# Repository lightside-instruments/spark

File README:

Spark is a modular open-source hardware platform
base board and enclosure for use as development kit for programmable
network elements.

The project includes KiCAD project with schematics
and PCB layout sources, BOM, and technical documentation for
production of board with 6x SFP+ interfaces and a 96board
extension interface for the connection of a control board
(FPGA or ASIC)  e.g. Ultra96 from Avnet
and up to 3 optional extension boards:
* glue logic for low speed signals from the optical modules
* GNSS controlled oscillators
* other interface boards, sensor boards, etc.

The project includes also technical documentation for production of
mechanical enclosure - 19 inch 1U rack mountable ESD Acrylic box compatibe
with the base board.

The project is published by Lightside Instruments AS
under TAPR Open Hardware License. Read the LICENSE file
for details.

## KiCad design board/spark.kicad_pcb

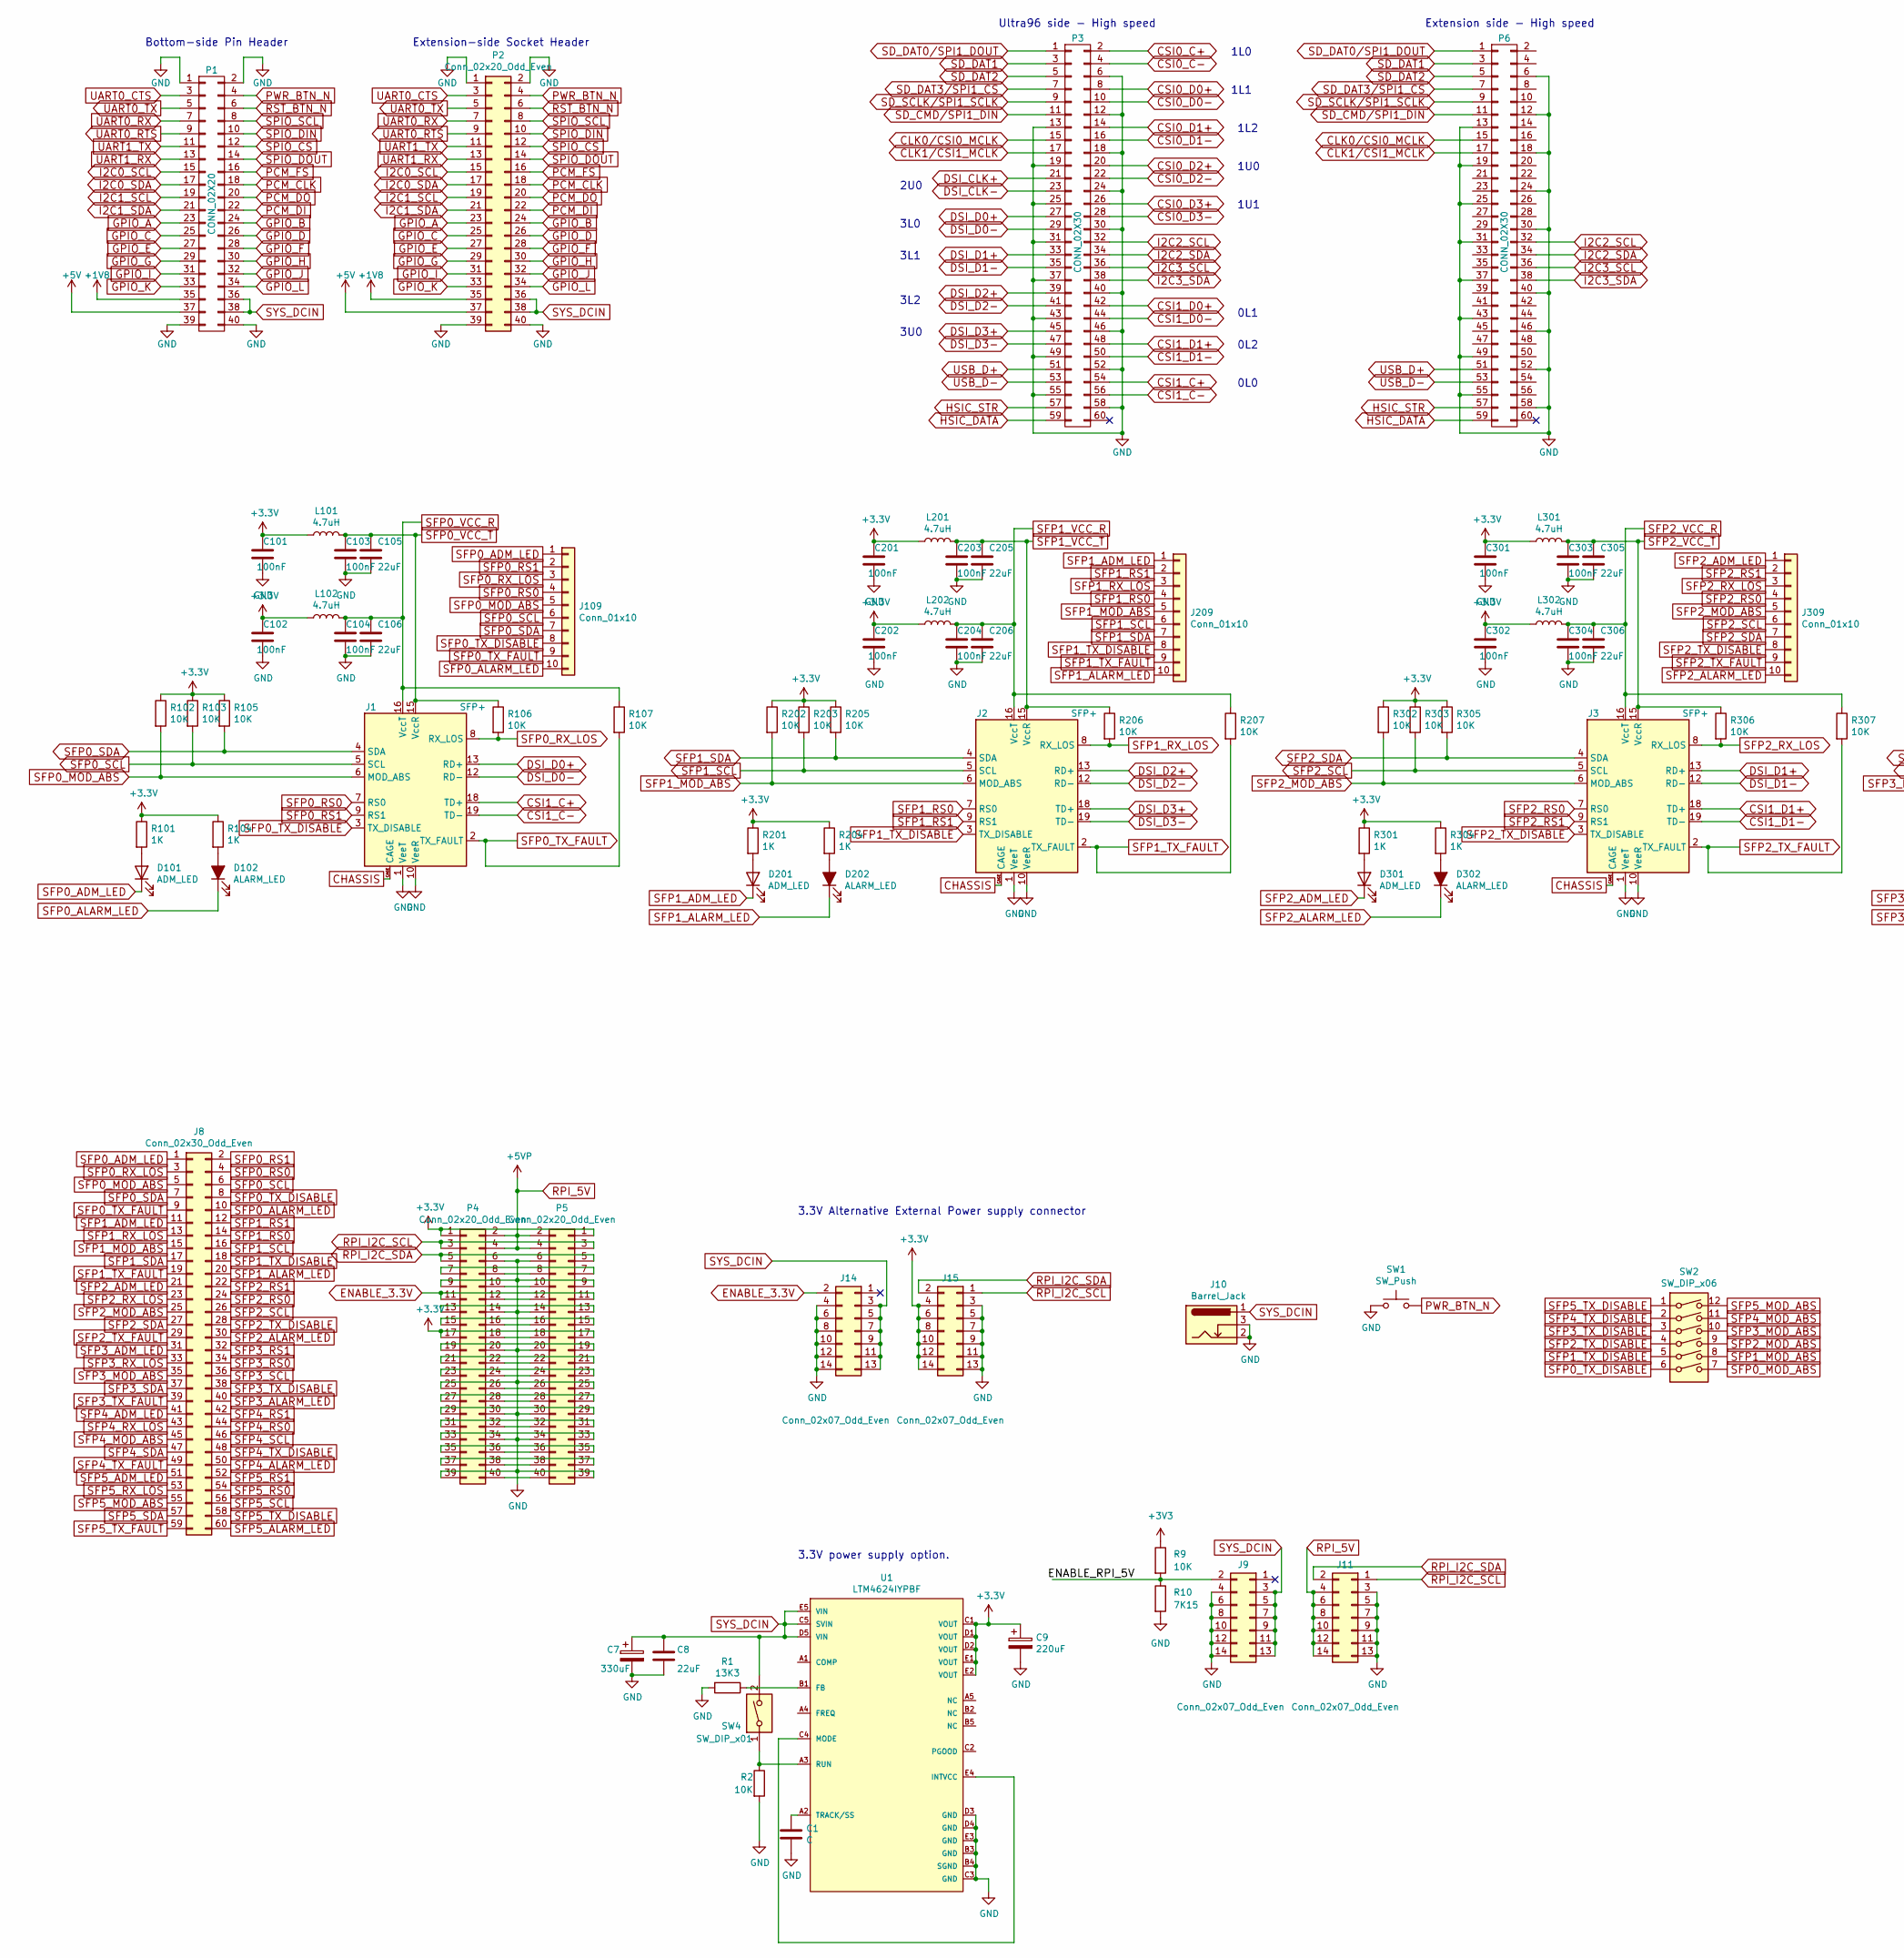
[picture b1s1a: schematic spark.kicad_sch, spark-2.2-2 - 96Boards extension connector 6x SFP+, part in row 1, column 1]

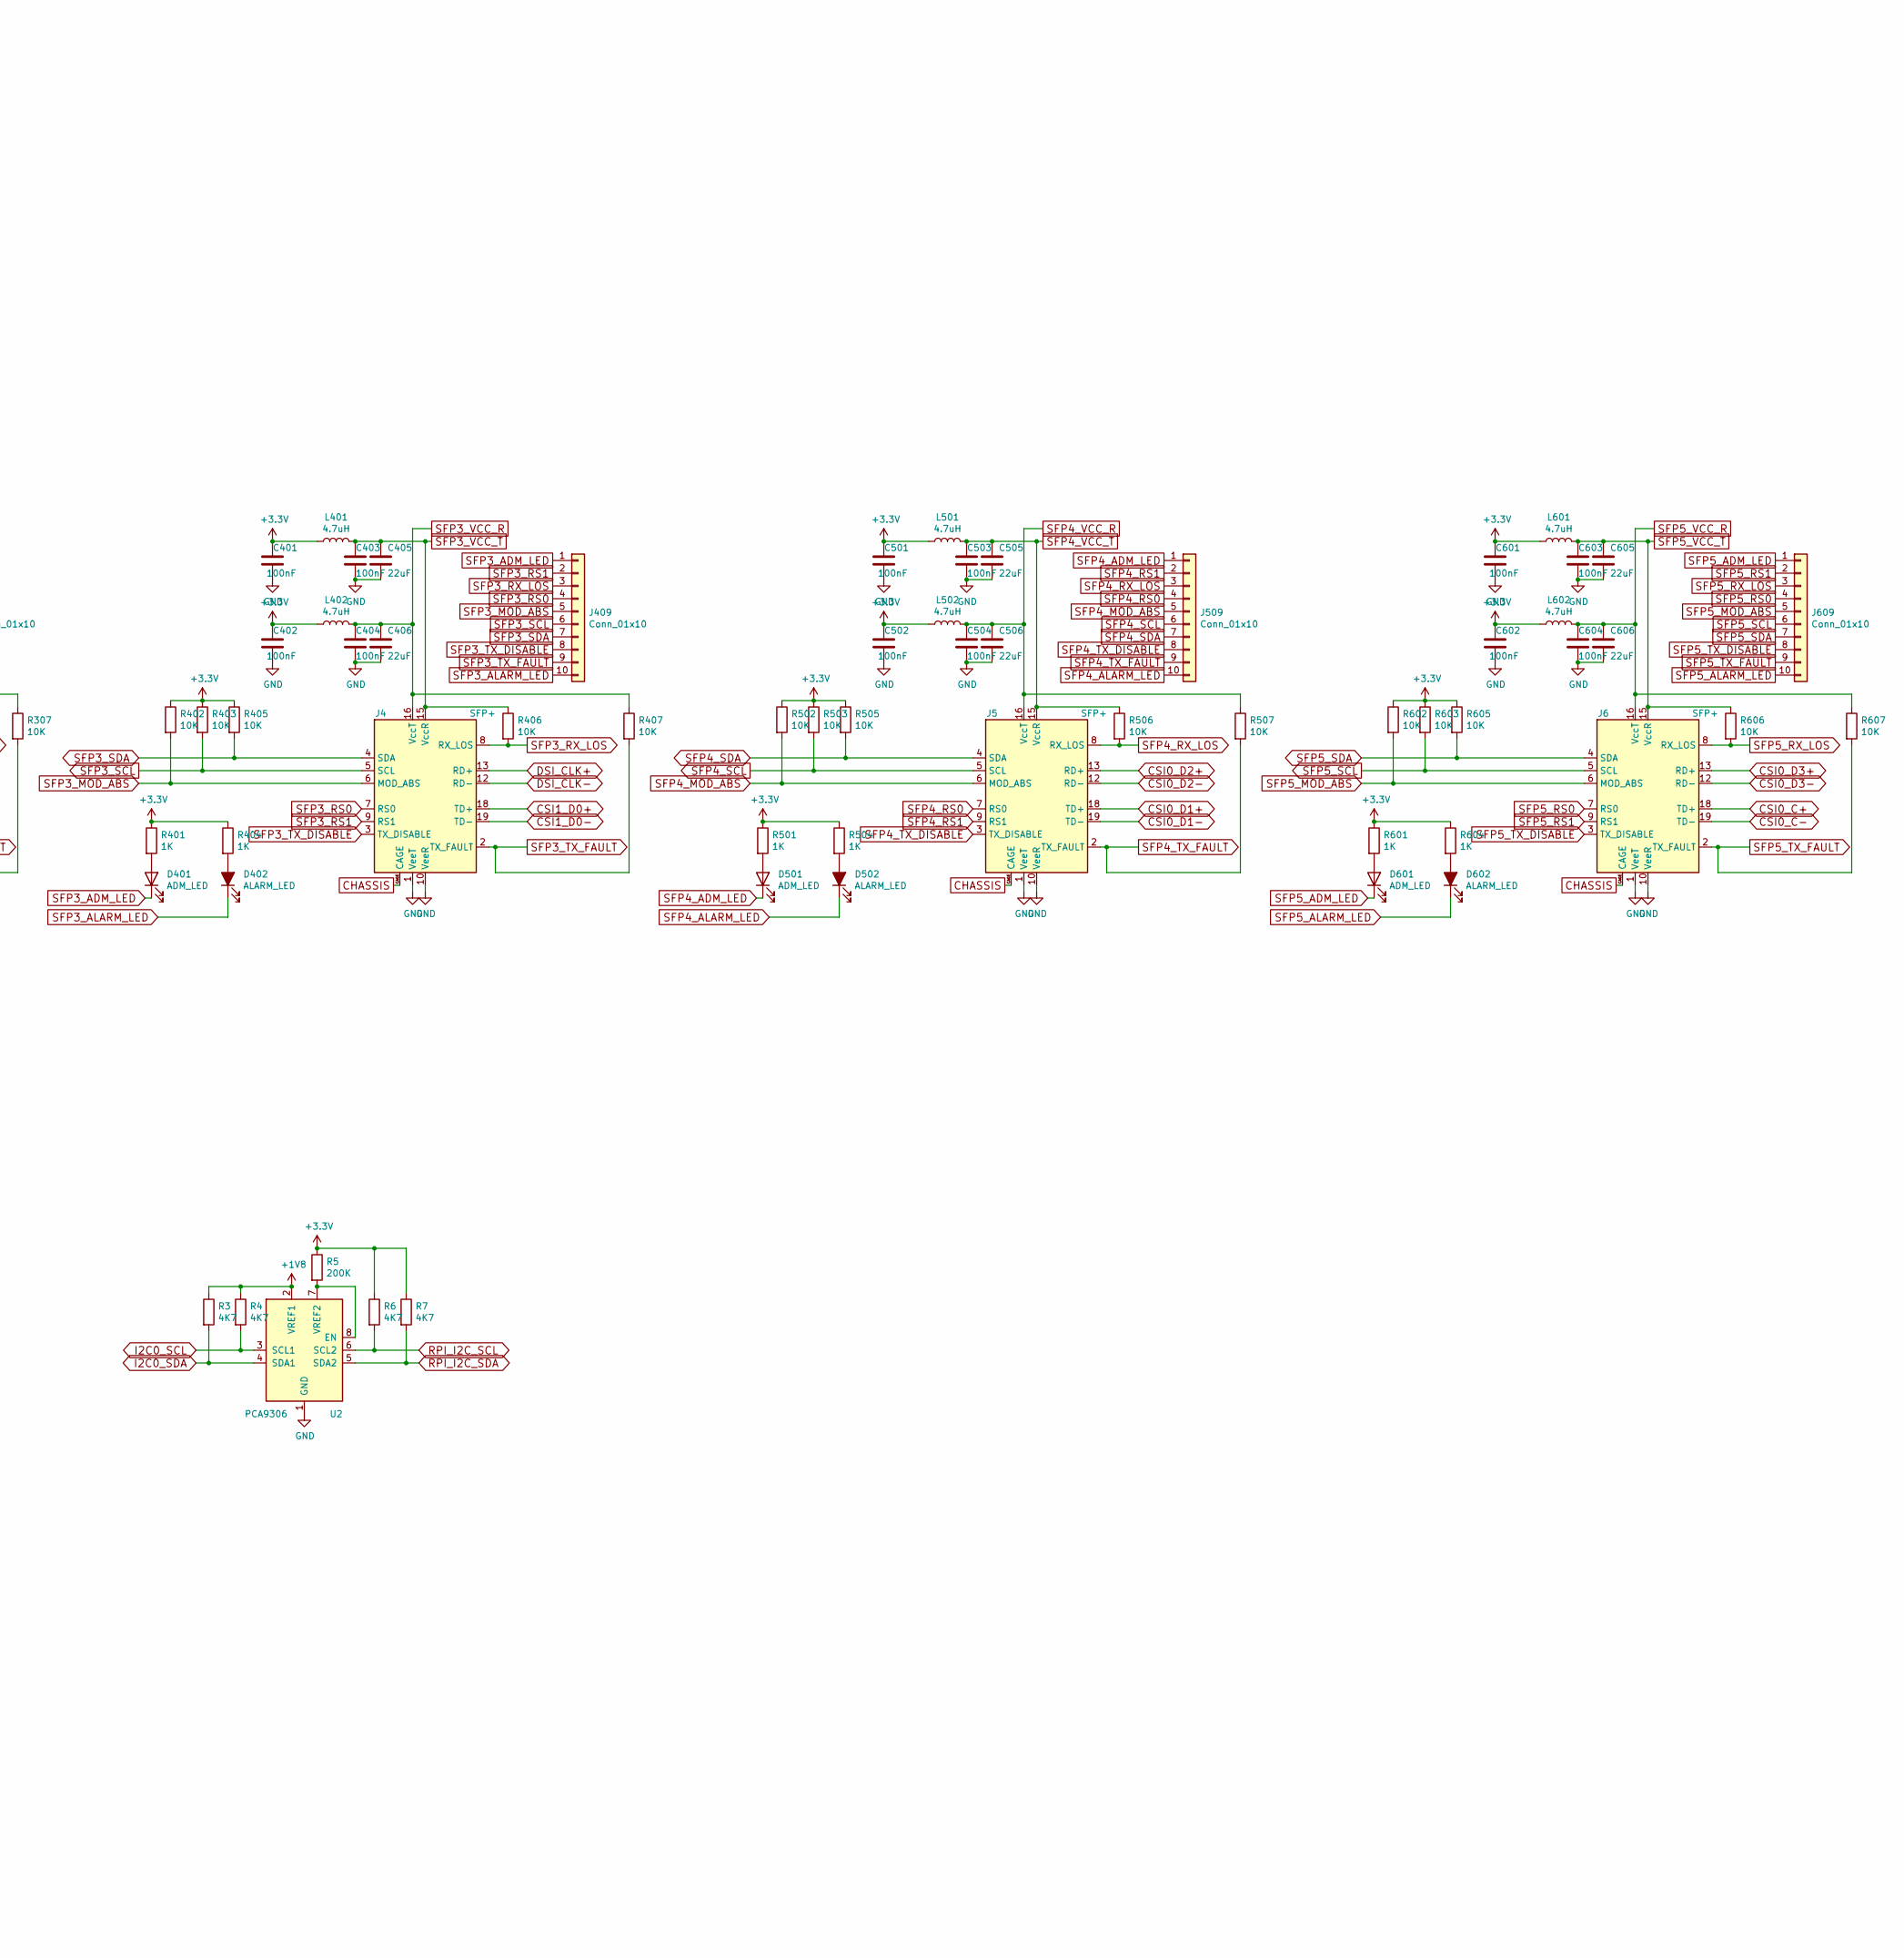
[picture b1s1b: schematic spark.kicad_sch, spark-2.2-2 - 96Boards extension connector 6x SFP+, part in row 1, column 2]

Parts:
C1: C; C_0402_1005Metric
C7: 330uF; CP_EIA-7343-31_Kemet-D
C8, C105, C106, C205, C206, C305, C306, C405, C406, C505, C506, C605, C606: 22uF; CP_EIA-3528-21_Kemet-B; Mfr Part # TAJB226K016TNJ
C9: 220uF; CP_EIA-7343-31_Kemet-D
C101, C102, C103, C104, C201, C202, C203, C204, C301, C302, C303, C304, C401, C402, C403, C404, C501, C502, C503, C504, C601, C602, C603, C604: 100nF; C_0402_1005Metric
D101, D201, D301, D401, D501, D601: ADM_LED; LED_0402_1005Metric
D102, D202, D302, D402, D502, D602: ALARM_LED; LED_0402_1005Metric
J1, J2, J3, J4, J5, J6: SFP+; molex-sfp-plus-747540-101
J8: Conn_02x30_Odd_Even; PinHeader_2x30_P2.00mm_Vertical_SMD
J9, J11, J14, J15: Conn_02x07_Odd_Even; PinSocket_2x07_P2.00mm_Vertical_SMD
J10: Barrel_Jack; PJ1-021-SMT-TR
J109, J209, J309, J409, J509, J609: Conn_01x10; sfp_header
L101, L102, L201, L202, L301, L302, L401, L402, L501, L502, L601, L602: 4.7uH; L_1210_3225Metric
P1: CONN_02X20; Pin_Header_SMD_2x20_Pitch2mm; Mfr Part # 87759-4051
P2: Conn_02x20_Odd_Even; Socket_Strip_SMD_2x20_Pitch2mm_Alignment_Pin
P3: CONN_02X30; 61083-063400LF; Mfr Part # 61083-064400LF
P4, P5: Conn_02x20_Odd_Even; PinSocket_2x20_P2.54mm_Vertical_Inverted_SMD_Alignment_Pin
P6: CONN_02X30; 5177983-2; Mfr Part # 5177983-2
R1: 13K3; R_0402_1005Metric
R2, R9, R102, R103, R105, R106, R107, R202, R203, R205, R206, R207, R302, R303, R305, R306, R307, R402, R403, R405, R406, R407, R502, R503, R505, R506, R507, R602, R603, R605, R606, R607: 10K; R_0402_1005Metric
R3, R4, R6, R7: 4K7; R_0402_1005Metric
R5: 200K; R_0402_1005Metric
R10: 7K15; R_0402_1005Metric
R101, R104, R201, R204, R301, R304, R401, R404, R501, R504, R601, R604: 1K; R_0402_1005Metric
SW1: SW_Push; SW_Tactile_SPST_Angled_PTS645Vx83-2LFS; Mfr Part # PTS645VK582LFS
SW2: SW_DIP_x06; SW_DIP_SPSTx06_Slide_Omron_A6H-6101_W6.15mm_P1.27mm; Mfr Part # A6H-6101
SW4: SW_DIP_x01; PinHeader_1x02_P2.54mm_Vertical
U1: LTM4624IYPBF; Analog_Devices_Inc-BGA-0-05-08-1905_Rev_C-0; output voltage 0.6-5.5V; mouser part number 584-LTM4624IY#PBF; digikey description DC DC CONVERTER 0.6-5.5V 4A
U2: PCA9306; SO-8_3.9x4.9mm_P1.27mm

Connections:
+1V8: P1.35, P2.35, R3.1, R4.1, U2.2 (VREF1)
+5V: P1.37, P2.37
/ENABLE_RPI_5V: J9.2, R9.2, R10.1
CHASSIS: J1.CAGE, J2.CAGE, J3.CAGE, J4.CAGE, J5.CAGE, J6.CAGE
CLK0/CSI0_MCLK: P3.15, P6.15
CLK1/CSI1_MCLK: P3.17, P6.17
CSI0_C+: J6.18 (TD+), P3.2
CSI0_C-: J6.19 (TD-), P3.4
CSI0_D0+: P3.8
CSI0_D0-: P3.10
CSI0_D1+: J5.18 (TD+), P3.14
CSI0_D1-: J5.19 (TD-), P3.16
CSI0_D2+: J5.13 (RD+), P3.20
CSI0_D2-: J5.12 (RD-), P3.22
CSI0_D3+: J6.13 (RD+), P3.26
CSI0_D3-: J6.12 (RD-), P3.28
CSI1_C+: J1.18 (TD+), P3.54
CSI1_C-: J1.19 (TD-), P3.56
CSI1_D0+: J4.18 (TD+), P3.42
CSI1_D0-: J4.19 (TD-), P3.44
CSI1_D1+: J3.18 (TD+), P3.48
CSI1_D1-: J3.19 (TD-), P3.50
DSI_CLK+: J4.13 (RD+), P3.21
DSI_CLK-: J4.12 (RD-), P3.23
DSI_D0+: J1.13 (RD+), P3.27
DSI_D0-: J1.12 (RD-), P3.29
DSI_D1+: J3.13 (RD+), P3.33
DSI_D1-: J3.12 (RD-), P3.35
DSI_D2+: J2.13 (RD+), P3.39
DSI_D2-: J2.12 (RD-), P3.41
DSI_D3+: J2.18 (TD+), P3.45
DSI_D3-: J2.19 (TD-), P3.47
ENABLE_3.3V: J14.2, P4.11, P5.11
GND: C1.2, C7.2, C8.2, C9.2, C101.2, C102.2, C103.2, C104.2, C105.2, C106.2, C201.2, C202.2, C203.2, C204.2, C205.2, C206.2, C301.2, C302.2, C303.2, C304.2, C305.2, C306.2, C401.2, C402.2, C403.2, C404.2, C405.2, C406.2, C501.2, C502.2, C503.2, C504.2, C505.2, C506.2, C601.2, C602.2, C603.2, C604.2, C605.2, C606.2, J1.1 (VeeT), J1.10 (VeeR), J1.11 (VeeR), J1.14 (VeeR), J1.17 (VeeT), J1.20 (VeeT), J2.1 (VeeT), J2.10 (VeeR), J2.11 (VeeR), J2.14 (VeeR), J2.17 (VeeT), J2.20 (VeeT), J3.1 (VeeT), J3.10 (VeeR), J3.11 (VeeR), J3.14 (VeeR), J3.17 (VeeT), J3.20 (VeeT), J4.1 (VeeT), J4.10 (VeeR), J4.11 (VeeR), J4.14 (VeeR), J4.17 (VeeT), J4.20 (VeeT), J5.1 (VeeT), J5.10 (VeeR), J5.11 (VeeR), J5.14 (VeeR), J5.17 (VeeT), J5.20 (VeeT), J6.1 (VeeT), J6.10 (VeeR), J6.11 (VeeR), J6.14 (VeeR), J6.17 (VeeT), J6.20 (VeeT), J9.4, J9.6, J9.8, J9.10, J9.12, J9.14, J10.2, J10.3, J11.3, J11.5, J11.7, J11.9, J11.11, J11.13, J14.4, J14.6, J14.8, J14.10, J14.12, J14.14, J15.3, J15.5, J15.7, J15.9, J15.11, J15.13, P1.1, P1.2, P1.39, P1.40, P2.1, P2.2, P2.39, P2.40, P3.6, P3.12, P3.13, P3.18, P3.19, P3.24, P3.25, P3.30, P3.31, P3.37, P3.40, P3.43, P3.46, P3.49, P3.52, P3.55, P3.58, P4.6, P4.9, P4.14, P4.20, P4.25, P4.30, P4.34, P4.39, P5.6, P5.9, P5.14, P5.20, P5.25, P5.30, P5.34, P5.39, P6.6, P6.12, P6.13, P6.18, P6.19, P6.24, P6.25, P6.30, P6.31, P6.37, P6.40, P6.43, P6.46, P6.49, P6.52, P6.55, P6.58, R1.2, R2.2, R10.2, SW1.1, U1.B3 (GND), U1.B4 (SGND), U1.C3 (GND), U1.D3 (GND), U1.D4 (GND), U1.E3 (GND), U2.1 (GND)
GPIO_A: P1.23, P2.23
GPIO_B: P1.24, P2.24
GPIO_C: P1.25, P2.25
GPIO_D: P1.26, P2.26
GPIO_E: P1.27, P2.27
GPIO_F: P1.28, P2.28
GPIO_G: P1.29, P2.29
GPIO_H: P1.30, P2.30
GPIO_I: P1.31, P2.31
GPIO_J: P1.32, P2.32
GPIO_K: P1.33, P2.33
GPIO_L: P1.34, P2.34
HSIC_DATA: P3.59, P6.59
HSIC_STR: P3.57, P6.57
I2C0_SCL: P1.15, P2.15, R4.2, U2.3 (SCL1)
I2C0_SDA: P1.17, P2.17, R3.2, U2.4 (SDA1)
I2C1_SCL: P1.19, P2.19
I2C1_SDA: P1.21, P2.21
I2C2_SCL: P3.32, P6.32
I2C2_SDA: P3.34, P6.34
I2C3_SCL: P3.36, P6.36
I2C3_SDA: P3.38, P6.38
unnamed: C1.1, U1.A2 (TRACK/SS)
unnamed: D101.2 (A), R101.2
unnamed: D102.2 (A), R104.2
unnamed: D201.2 (A), R201.2
unnamed: D202.2 (A), R204.2
unnamed: D301.2 (A), R301.2
unnamed: D302.2 (A), R304.2
unnamed: D401.2 (A), R401.2
unnamed: D402.2 (A), R404.2
unnamed: D501.2 (A), R501.2
unnamed: D502.2 (A), R504.2
unnamed: D601.2 (A), R601.2
unnamed: D602.2 (A), R604.2
unnamed: P4.7, P5.7
unnamed: P4.8, P5.8
unnamed: P4.10, P5.10
unnamed: P4.12, P5.12
unnamed: P4.13, P5.13
unnamed: P4.15, P5.15
unnamed: P4.16, P5.16
unnamed: P4.18, P5.18
unnamed: P4.19, P5.19
unnamed: P4.21, P5.21
unnamed: P4.22, P5.22
unnamed: P4.23, P5.23
unnamed: P4.24, P5.24
unnamed: P4.26, P5.26
unnamed: P4.27, P5.27
unnamed: P4.28, P5.28
unnamed: P4.29, P5.29
unnamed: P4.31, P5.31
unnamed: P4.32, P5.32
unnamed: P4.33, P5.33
unnamed: P4.35, P5.35
unnamed: P4.36, P5.36
unnamed: P4.37, P5.37
unnamed: P4.38, P5.38
unnamed: P4.40, P5.40
unnamed: R1.1, U1.B1 (FB)
unnamed: R2.1, SW4.1, U1.A3 (RUN)
unnamed: R5.2, U2.7 (VREF2), U2.8 (EN)
unnamed: U1.C4 (MODE), U1.E4 (INTVCC)
PCM_CLK: P1.18, P2.18
PCM_DI: P1.22, P2.22
PCM_DO: P1.20, P2.20
PCM_FS: P1.16, P2.16
PWR_BTN_N: P1.4, P2.4, SW1.2
RPI_5V: J11.4, J11.6, J11.8, J11.10, J11.12, J11.14, P4.2, P4.4, P5.2, P5.4
RPI_I2C_SCL: J11.1, J15.1, P4.3, P5.3, R6.2, U2.6 (SCL2)
RPI_I2C_SDA: J11.2, J15.2, P4.5, P5.5, R7.2, U2.5 (SDA2)
RST_BTN_N: P1.6, P2.6
SD_CMD/SPI1_DIN: P3.11, P6.11
SD_DAT0/SPI1_DOUT: P3.1, P6.1
SD_DAT1: P3.3, P6.3
SD_DAT2: P3.5, P6.5
SD_DAT3/SPI1_CS: P3.7, P6.7
SD_SCLK/SPI1_SCLK: P3.9, P6.9
SFP0_ADM_LED: D101.1 (K), J8.1, J109.1
SFP0_ALARM_LED: D102.1 (K), J8.10, J109.10
SFP0_MOD_ABS: J1.6 (MOD_ABS), J8.5, J109.5, R102.2, SW2.7
SFP0_RS0: J1.7 (RS0), J8.4, J109.4
SFP0_RS1: J1.9 (RS1), J8.2, J109.2
SFP0_RX_LOS: J1.8 (RX_LOS), J8.3, J109.3, R106.2
SFP0_SCL: J1.5 (SCL), J8.6, J109.6, R103.2
SFP0_SDA: J1.4 (SDA), J8.7, J109.7, R105.2
SFP0_TX_DISABLE: J1.3 (TX_DISABLE), J8.8, J109.8, SW2.6
SFP0_TX_FAULT: J1.2 (TX_FAULT), J8.9, J109.9, R107.2
SFP0_VCC_R: C104.1, C106.1, J1.16 (VccT), L102.2, R107.1
SFP0_VCC_T: C103.1, C105.1, J1.15 (VccR), L101.2, R106.1
SFP1_ADM_LED: D201.1 (K), J8.11, J209.1
SFP1_ALARM_LED: D202.1 (K), J8.20, J209.10
SFP1_MOD_ABS: J2.6 (MOD_ABS), J8.15, J209.5, R202.2, SW2.8
SFP1_RS0: J2.7 (RS0), J8.14, J209.4
SFP1_RS1: J2.9 (RS1), J8.12, J209.2
SFP1_RX_LOS: J2.8 (RX_LOS), J8.13, J209.3, R206.2
SFP1_SCL: J2.5 (SCL), J8.16, J209.6, R203.2
SFP1_SDA: J2.4 (SDA), J8.17, J209.7, R205.2
SFP1_TX_DISABLE: J2.3 (TX_DISABLE), J8.18, J209.8, SW2.5
SFP1_TX_FAULT: J2.2 (TX_FAULT), J8.19, J209.9, R207.2
SFP1_VCC_R: C204.1, C206.1, J2.16 (VccT), L202.2, R207.1
SFP1_VCC_T: C203.1, C205.1, J2.15 (VccR), L201.2, R206.1
SFP2_ADM_LED: D301.1 (K), J8.21, J309.1
SFP2_ALARM_LED: D302.1 (K), J8.30, J309.10
SFP2_MOD_ABS: J3.6 (MOD_ABS), J8.25, J309.5, R302.2, SW2.9
SFP2_RS0: J3.7 (RS0), J8.24, J309.4
SFP2_RS1: J3.9 (RS1), J8.22, J309.2
SFP2_RX_LOS: J3.8 (RX_LOS), J8.23, J309.3, R306.2
SFP2_SCL: J3.5 (SCL), J8.26, J309.6, R303.2
SFP2_SDA: J3.4 (SDA), J8.27, J309.7, R305.2
SFP2_TX_DISABLE: J3.3 (TX_DISABLE), J8.28, J309.8, SW2.4
SFP2_TX_FAULT: J3.2 (TX_FAULT), J8.29, J309.9, R307.2
SFP2_VCC_R: C304.1, C306.1, J3.16 (VccT), L302.2, R307.1
SFP2_VCC_T: C303.1, C305.1, J3.15 (VccR), L301.2, R306.1
SFP3_ADM_LED: D401.1 (K), J8.31, J409.1
SFP3_ALARM_LED: D402.1 (K), J8.40, J409.10
SFP3_MOD_ABS: J4.6 (MOD_ABS), J8.35, J409.5, R402.2, SW2.10
SFP3_RS0: J4.7 (RS0), J8.34, J409.4
SFP3_RS1: J4.9 (RS1), J8.32, J409.2
SFP3_RX_LOS: J4.8 (RX_LOS), J8.33, J409.3, R406.2
SFP3_SCL: J4.5 (SCL), J8.36, J409.6, R403.2
SFP3_SDA: J4.4 (SDA), J8.37, J409.7, R405.2
SFP3_TX_DISABLE: J4.3 (TX_DISABLE), J8.38, J409.8, SW2.3
SFP3_TX_FAULT: J4.2 (TX_FAULT), J8.39, J409.9, R407.2
SFP3_VCC_R: C404.1, C406.1, J4.16 (VccT), L402.2, R407.1
SFP3_VCC_T: C403.1, C405.1, J4.15 (VccR), L401.2, R406.1
SFP4_ADM_LED: D501.1 (K), J8.41, J509.1
SFP4_ALARM_LED: D502.1 (K), J8.50, J509.10
SFP4_MOD_ABS: J5.6 (MOD_ABS), J8.45, J509.5, R502.2, SW2.11
SFP4_RS0: J5.7 (RS0), J8.44, J509.4
SFP4_RS1: J5.9 (RS1), J8.42, J509.2
SFP4_RX_LOS: J5.8 (RX_LOS), J8.43, J509.3, R506.2
SFP4_SCL: J5.5 (SCL), J8.46, J509.6, R503.2
SFP4_SDA: J5.4 (SDA), J8.47, J509.7, R505.2
SFP4_TX_DISABLE: J5.3 (TX_DISABLE), J8.48, J509.8, SW2.2
SFP4_TX_FAULT: J5.2 (TX_FAULT), J8.49, J509.9, R507.2
SFP4_VCC_R: C504.1, C506.1, J5.16 (VccT), L502.2, R507.1
SFP4_VCC_T: C503.1, C505.1, J5.15 (VccR), L501.2, R506.1
SFP5_ADM_LED: D601.1 (K), J8.51, J609.1
SFP5_ALARM_LED: D602.1 (K), J8.60, J609.10
SFP5_MOD_ABS: J6.6 (MOD_ABS), J8.55, J609.5, R602.2, SW2.12
SFP5_RS0: J6.7 (RS0), J8.54, J609.4
SFP5_RS1: J6.9 (RS1), J8.52, J609.2
SFP5_RX_LOS: J6.8 (RX_LOS), J8.53, J609.3, R606.2
SFP5_SCL: J6.5 (SCL), J8.56, J609.6, R603.2
SFP5_SDA: J6.4 (SDA), J8.57, J609.7, R605.2
SFP5_TX_DISABLE: J6.3 (TX_DISABLE), J8.58, J609.8, SW2.1
SFP5_TX_FAULT: J6.2 (TX_FAULT), J8.59, J609.9, R607.2
SFP5_VCC_R: C604.1, C606.1, J6.16 (VccT), L602.2, R607.1
SFP5_VCC_T: C603.1, C605.1, J6.15 (VccR), L601.2, R606.1
SPIO_CS: P1.12, P2.12
SPIO_DIN: P1.10, P2.10
SPIO_DOUT: P1.14, P2.14
SPIO_SCL: P1.8, P2.8
SYS_DCIN: C7.1, C8.1, J9.3, J9.5, J9.7, J9.9, J9.11, J9.13, J10.1, J14.3, J14.5, J14.7, J14.9, J14.11, J14.13, P1.36, P1.38, P2.36, P2.38, SW4.2, U1.C5 (SVIN), U1.D5 (VIN), U1.E5 (VIN)
UART0_CTS: P1.3, P2.3
UART0_RTS: P1.9, P2.9
UART0_RX: P1.7, P2.7
UART0_TX: P1.5, P2.5
UART1_RX: P1.13, P2.13
UART1_TX: P1.11, P2.11
USB_D+: P3.51, P6.51
USB_D-: P3.53, P6.53

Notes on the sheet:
1U1
3.3V power supply option.
Extension side - High speed
1L1
1U0
3L2
0L2
3L1
3U0
Ultra96 side - High speed
Bottom-side Pin Header
2U0
Extension-side Socket Header
3.3V Alternative External Power supply connector
0L1
3L0
0L0
1L2
1L0

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
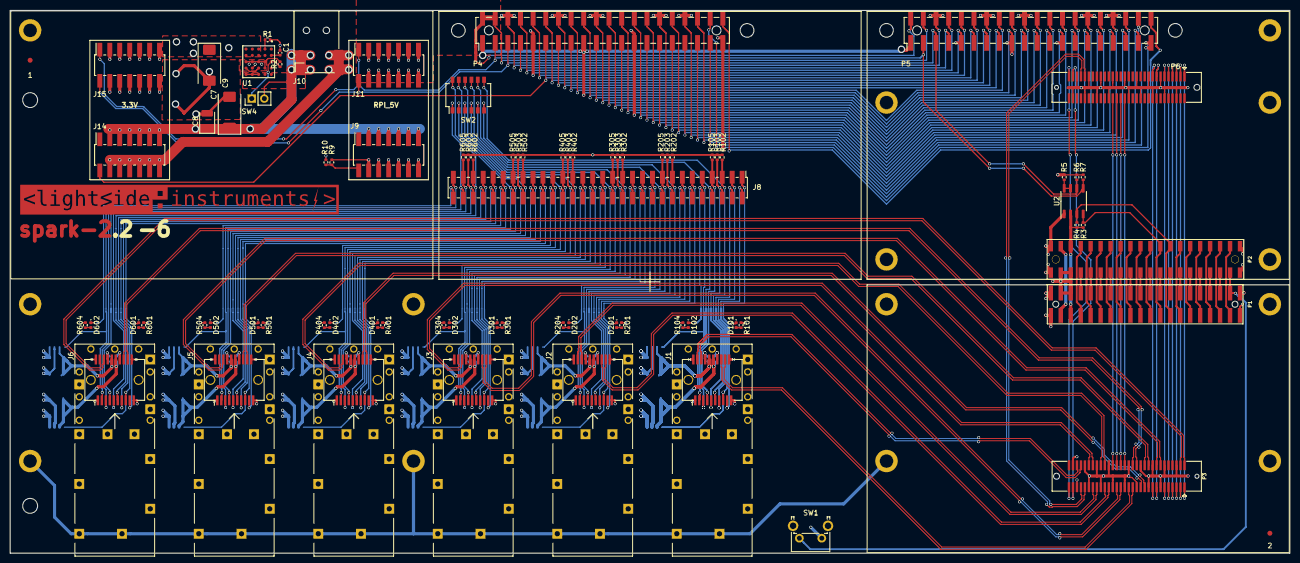
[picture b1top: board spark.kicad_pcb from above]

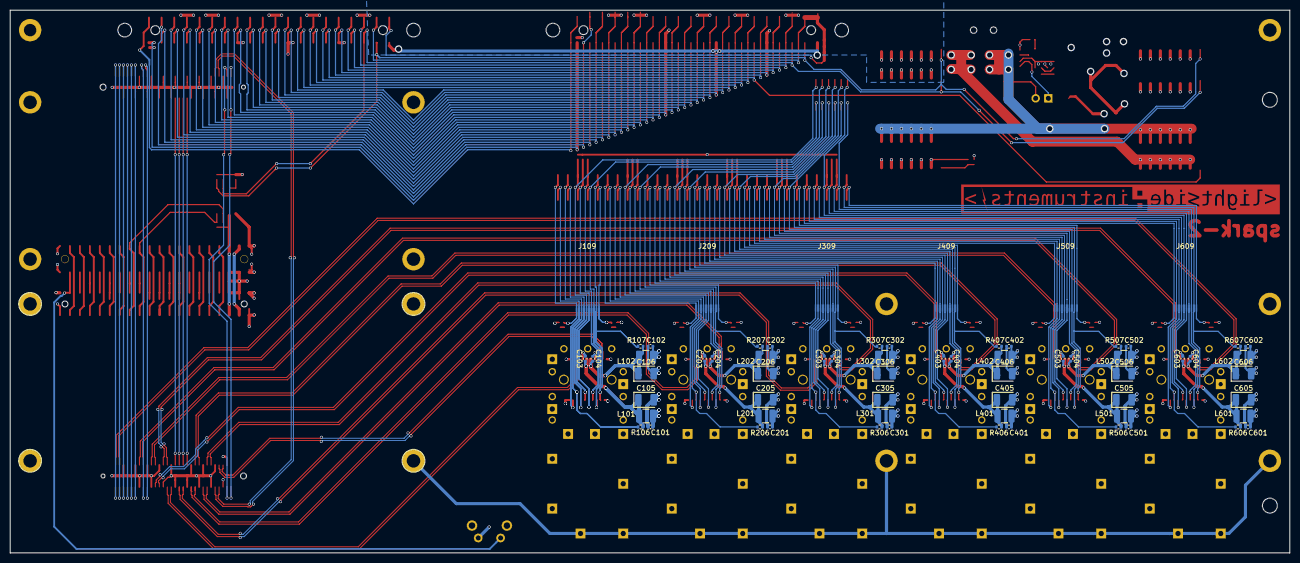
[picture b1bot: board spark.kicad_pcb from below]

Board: 4 copper layers, 257.0 x 109.0 mm, 146 parts (66 on the bottom side), 197 nets.

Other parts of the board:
1, 2: Fiducial_1mm_Mask3mm

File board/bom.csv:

Reference,Quantity,Identifier,footprint,Value,Tolerance,Voltage,Current,Power,Mfr,Mfr Part #,Notes
P1,1,,96boards:Pin_Header_SMD_2x20_Pitch2mm,CONN_02X20,,,,,Molex,87759-4051,
P3,1,,96boards:61083-063400LF,CONN_02X30,,,,,Amphenol,61083-064400LF,
J1_1;J2_1;J3_1;J4_1;J5_1;J6_1,6,,spark:molex-sfp-plus-747540-101,SFP+,,,,,,74754-0101,
J1;J2;J3;J4;J5;J6,6,,spark:molex-sfp-plus-747540-101,SFP+,,,,,,74441-0001,
J1_2;J2_2;J3_2;J4_2;J5_2;J6_2,6,,spark:molex-sfp-plus-747540-101,SFP+,,,,,,74754-0011,
J7,1,,spark:R-PDSS-B11,PTH08T221W,,,,,,PTH08T221WAZ,
R102;R103;R105;R106;R107;R202;R203;R205;R206;R207;R302;R303;R305;R306;R307;R402;R403;R405;R406;R407;R502;R503;R505;R506;R507;R602;R603;R605;R606;R607;R9,31,,Resistor_SMD:R_0402_1005Metric,10K,,,,,,CRCW040210K0FKEDC,
C102;C104;C101;C103;C202;C204;C201;C203;C302;C304;C301;C303;C402;C404;C401;C403;C502;C504;C501;C503;C602;C604;C601;C603,24,,Capacitor_SMD:C_0402_1005Metric,100nF,,,,,,885012205037,
J10,1,,spark:PJ1-021-SMT-TR,Barrel_Jack,,,,,,PJ1-021-SMT-TR,
L102;L101;L202;L201;L302;L301;L402;L401;L502;L501;L602;L601,12,,Inductor_SMD:L_1210_3225Metric,4.7uH,,,,,,CM322522-4R7JL,
C106;C105;C8;C206;C205;C306;C305;C406;C405;C506;C505;C606;C605,13,,Capacitor_SMD:C_1210_3225Metric,22uF,,>=16V,,,,F931C226MBAAJ6,TAJB226M016SNJ
D101;D201;D301;D401;D501;D601,6,,LED_SMD:LED_0402_1005Metric,ADM_LED,,,,,,"
150040VS73240",
R101;R104;R201;R204;R301;R304;R401;R404;R501;R504;R601;R604,12,,Resistor_SMD:R_0402_1005Metric,1K,,,,,,RR0510P-102-D,
D102;D202;D302;D402;D502;D602,6,,LED_SMD:LED_0402_1005Metric,ALARM_LED,,,,,,"
150040VS73240",
R8,1,,Resistor_SMD:R_0402_1005Metric,1K21,,,,,,ERJ-2RKF1211X,
C7,1,,Capacitor_Tantalum_SMD:CP_EIA-7343-31_Kemet-D,330uF,,,,,,T491D227M016AT,
C9,1,,Capacitor_Tantalum_SMD:CP_EIA-7343-31_Kemet-D,220uF,,,,,,T491D227M016AT,
P2,1,,96boards:Socket_Strip_SMD_2x20_Pitch2mm,Conn_02x20_Odd_Even,,,,,Amphenol,55510-140LF,
J8_1;J8_2,2,,Connector_PinHeader_2.00mm:PinHeader_2x30_P2.00mm_Vertical_SMD,Conn_02x30_Odd_Even,,,,,Samtec,TMM-130-01-L-D-SM,Or 2x TMM-115-01-L-D-SM
P5;P4,2,,Connector_PinHeader_2.54mm:PinHeader_2x20_P2.54mm_Vertical_SMD,Conn_02x20_Odd_Even,,,,,Harwin,M20-7812045,
SW2,1,,Button_Switch_SMD:SW_DIP_SPSTx06_Slide_Omron_A6H-6101_W6.15mm_P1.27mm,SW_DIP_x06,,,,,,A6H-6101,
P6,1,,spark:5177983-2,CONN_02X30,,,,,TE CONNECTIVITY,1-5177983-2,
SW1,1,,Button_Switch_THT:SW_Tactile_SPST_Angled_PTS645Vx83-2LFS,SW_Push,,,,,,PTS645VK582LFS,
R1,1,*,,13.3K,,,,,,ERA-2AEB1332X,
U1,1,*,,,,,,,,LTM4624IY#PBF,
U2,1,,Package_SO:SO-8_3.9x4.9mm_P1.27mm,PCA9306,,,,,,PCA9306D,
R3;R4;R6;R7,4,,Resistor_SMD:R_0402_1005Metric,4K7,,,,,,CRCW04024K70FKED,
R5,1,,Resistor_SMD:R_0402_1005Metric,200K,,,,,,AC0402FR-7W200KL,
J9;J11,2,,spark:Socket_Strip_SMD_2x6_Pitch2mm,Conn_02x06_Odd_Even,,,,,,M20-7810645,
SW3;SW4,1,,Connector_PinHeader_2.54mm:PinHeader_1x02_P2.54mm_Vertical,SW_DIP_x01,,,,,,87224-2,
R7,1,,Resistor_SMD:R_0402_1005Metric,7K15,,,,,,CR0402-FX-7151GLF,

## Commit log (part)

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2023-09-14 Release 2.0-12
2023-09-20 Release 2.0-13
2023-09-22 Release 2.1
2023-09-28 Release 2.2
2024-05-27 Release 2.2-1
2024-05-27 Release 2.2-2
2024-06-14 Release 2.2-3
2026-04-23 Release 2.2-4
